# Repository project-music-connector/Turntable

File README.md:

# Turntable

The Turntable (inspired by Avoka's [Dyskograf](https://www.avoka.fr/portfolio/dyskograf/)) is an Arduino-powered turntable for which you can draw your own "vinyls". These drawings on circular discs, detected by infrared sensors, are transformed into looping music.
A Processing code reads the sensor data and interprets it, playing or generating sounds using the Processing 3 Sound library.

<br />This work is licensed under a <a rel="license" href="http://creativecommons.org/licenses/by-sa/4.0/">Creative Commons Attribution-ShareAlike 4.0 International License</a>.

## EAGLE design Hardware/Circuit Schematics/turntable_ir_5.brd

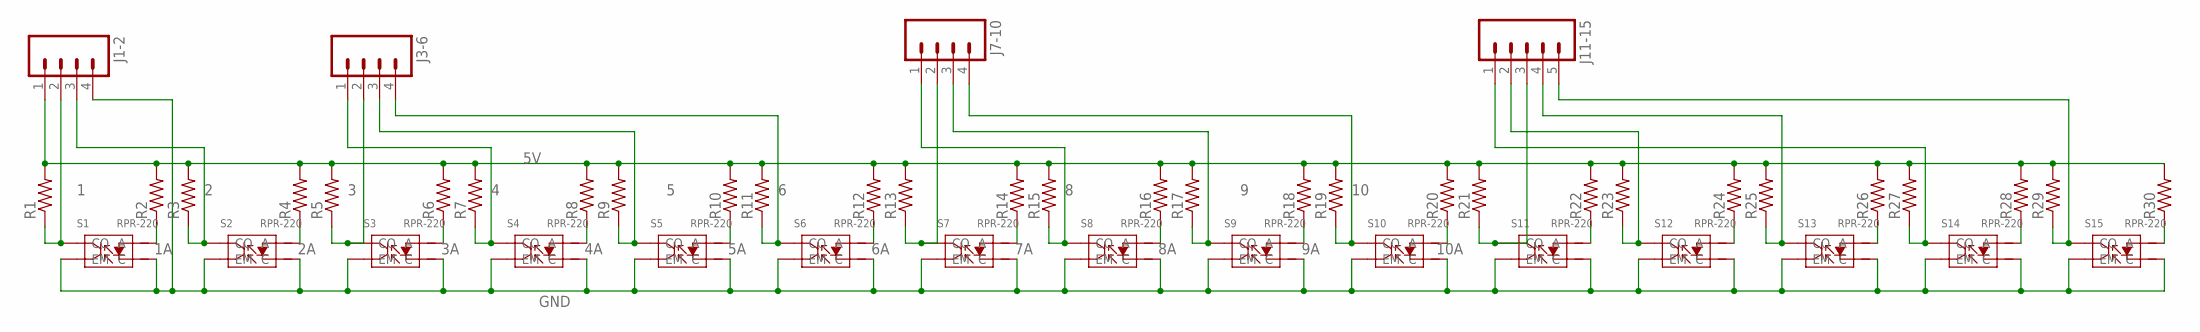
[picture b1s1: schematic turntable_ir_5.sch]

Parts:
J1-2, J3-6, J7-10: M04NO_SILK_ALL_ROUND; 1X04_NO_SILK_ALL_ROUND
J11-15: M05NO_SILK; 1X05_NO_SILK
R1, R2, R3, R4, R5, R6, R7, R8, R9, R10, R11, R12, R13, R14, R15, R16, R17, R18, R19, R20, R21, R22, R23, R24, R25, R26, R27, R28, R29, R30: RESISTOR1206; 1206
S1, S2, S3, S4, S5, S6, S7, S8, S9, S10, S11, S12, S13, S14, S15: RPR-220; RPR-220-6.4X4.9X6.5

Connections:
1: J1-2.2, R1.1, S1.P$4 (CO)
1A: R2.1, S1.P$1 (A)
2: J1-2.3, R3.1, S2.P$4 (CO)
2A: R4.1, S2.P$1 (A)
3: J3-6.2, R5.1, S3.P$4 (CO)
3A: R6.1, S3.P$1 (A)
4: J3-6.1, R7.1, S4.P$4 (CO)
4A: R8.1, S4.P$1 (A)
5: J3-6.3, R9.1, S5.P$4 (CO)
5A: R10.1, S5.P$1 (A)
5V: J1-2.1, R1.2, R2.2, R3.2, R4.2, R5.2, R6.2, R7.2, R8.2, R9.2, R10.2, R11.2, R12.2, R13.2, R14.2, R15.2, R16.2, R17.2, R18.2, R19.2, R20.2, R21.2, R22.2, R23.2, R24.2, R25.2, R26.2, R27.2, R28.2, R29.2, R30.2
6: J3-6.4, R11.1, S6.P$4 (CO)
6A: R12.1, S6.P$1 (A)
7: J7-10.2, R13.1, S7.P$4 (CO)
7A: R14.1, S7.P$1 (A)
8: J7-10.1, R15.1, S8.P$4 (CO)
8A: R16.1, S8.P$1 (A)
9: J7-10.3, R17.1, S9.P$4 (CO)
9A: R18.1, S9.P$1 (A)
10: J7-10.4, R19.1, S10.P$4 (CO)
10A: R20.1, S10.P$1 (A)
11: J11-15.3, R21.1, S11.P$4 (CO)
11A: R22.1, S11.P$1 (A)
12: J11-15.2, R23.1, S12.P$4 (CO)
12A: R24.1, S12.P$1 (A)
13: J11-15.4, R25.1, S13.P$4 (CO)
13A: R26.1, S13.P$1 (A)
14: J11-15.1, R27.1, S14.P$4 (CO)
14A: R28.1, S14.P$1 (A)
15: J11-15.5, R29.1, S15.P$4 (CO)
15A: R30.1, S15.P$1 (A)
GND: J1-2.4, S1.P$2 (C), S1.P$3 (EM), S2.P$2 (C), S2.P$3 (EM), S3.P$2 (C), S3.P$3 (EM), S4.P$2 (C), S4.P$3 (EM), S5.P$2 (C), S5.P$3 (EM), S6.P$2 (C), S6.P$3 (EM), S7.P$2 (C), S7.P$3 (EM), S8.P$2 (C), S8.P$3 (EM), S9.P$2 (C), S9.P$3 (EM), S10.P$2 (C), S10.P$3 (EM), S11.P$2 (C), S11.P$3 (EM), S12.P$2 (C), S12.P$3 (EM), S13.P$2 (C), S13.P$3 (EM), S14.P$2 (C), S14.P$3 (EM), S15.P$2 (C), S15.P$3 (EM)

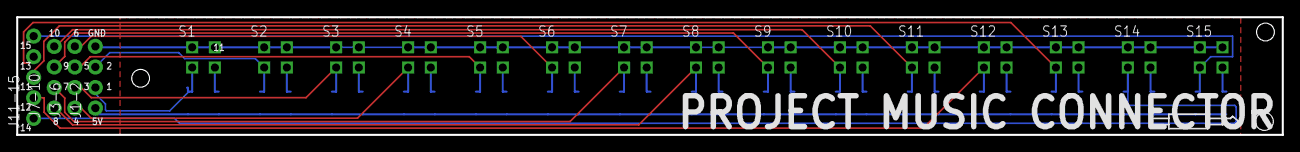
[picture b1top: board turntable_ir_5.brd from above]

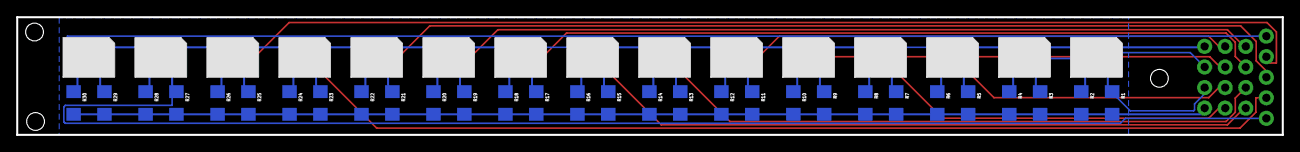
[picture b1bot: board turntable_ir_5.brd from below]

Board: 2 copper layers, 156.3 x 14.5 mm, 49 parts (30 on the bottom side), 32 nets.

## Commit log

2016-08-27 Fixed link
2016-08-27 Add Processing 3 mention
2016-08-28 Add Arduino files
    Arduino.ino outputs the data in DEC form so that Processing may read it.
    Arduino_test.ino outputs the data in a form most convenient for reading
    it with the serial monitor or plotter. This is the code we used to test
    the sensors.
2016-08-28 Add Processing code and sound files
    Has not been tested yet. Includes soundTypes 1 and 2.
2016-09-01 Rename Arduino_test.ino to Arduino_test_IRsensors.ino
2016-09-01 Added switches and changed array names
2016-09-03 Modified initialization of collection array
    After Building Session #3
2016-09-03 Create Hardware folder for data sheets and CAD files
2016-09-03 Add switches and potentiometer
2016-09-06 Increase delay
    This seems to solve our speed issues in Processing.
2016-09-07 Building Session 4
2016-09-07 Create Processing_test2
2016-09-07 Rename Processing_test2 to Processing_test2.pde
2016-09-07 Added changes from Processing_test_2, fixed bug
2016-09-07 Revert "Delete Arduino.ino"
    This reverts commit e10e111698f22d2bb6d359d08de0e31ea692eceb.
2016-09-11 Add switch to control speed of motor
2016-09-11 Replaced switch by potentiometer for motor speed
2016-09-11 Added and renamed stl files
2016-09-17 Add circuit schematics
2016-09-17 Create 3D-Printed Parts folder
2016-09-17 Revert "Add circuit schematics"
    This reverts commit 2bf2f11e3ec718a38d9ed1d62c2e9a69b671a327.
2016-09-17 Reorganized folder
2016-09-22 Add sounds
2016-09-22 Add piano sounds
2016-09-24 Update pins
2016-09-26 Add running average to smoothen sensor signal
2016-09-26 Processing 1 (#2)
    * Add files via upload
    * Add running average to smoothen sensor signal
2016-09-27 Change switch
2016-09-29 Create LICENSE
2016-09-29 Rename LICENSE to LICENSE.txt
2016-09-30 Add guitar sounds
2016-09-30 Update switch
2016-10-01 Add serial comma and processing sounds
2016-10-01 Add threshold modifications
2016-10-01 Stop generated sounds when changing soundType
2016-10-07 Last-minute changes
2016-10-16 Remove EAGLE schematic
2017-10-18 Changed arduino code to include new motor and pull down resistors
2017-10-18 update hardware
2017-10-20 Update code
    Arduino code: add new pins, edit motor code
    Processing code: add new pins with duplicate sounds
2017-10-21 Fix motor issues. Turntable now working.
2017-10-21 change threshold
2017-10-23 last minute changes from mfa2017

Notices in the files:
parts and their libraries:
SparkFun-Connectors: Licensing: Creative Commons ShareAlike 4.0 International - https://creativecommons.org/licenses/by-sa/4.0
